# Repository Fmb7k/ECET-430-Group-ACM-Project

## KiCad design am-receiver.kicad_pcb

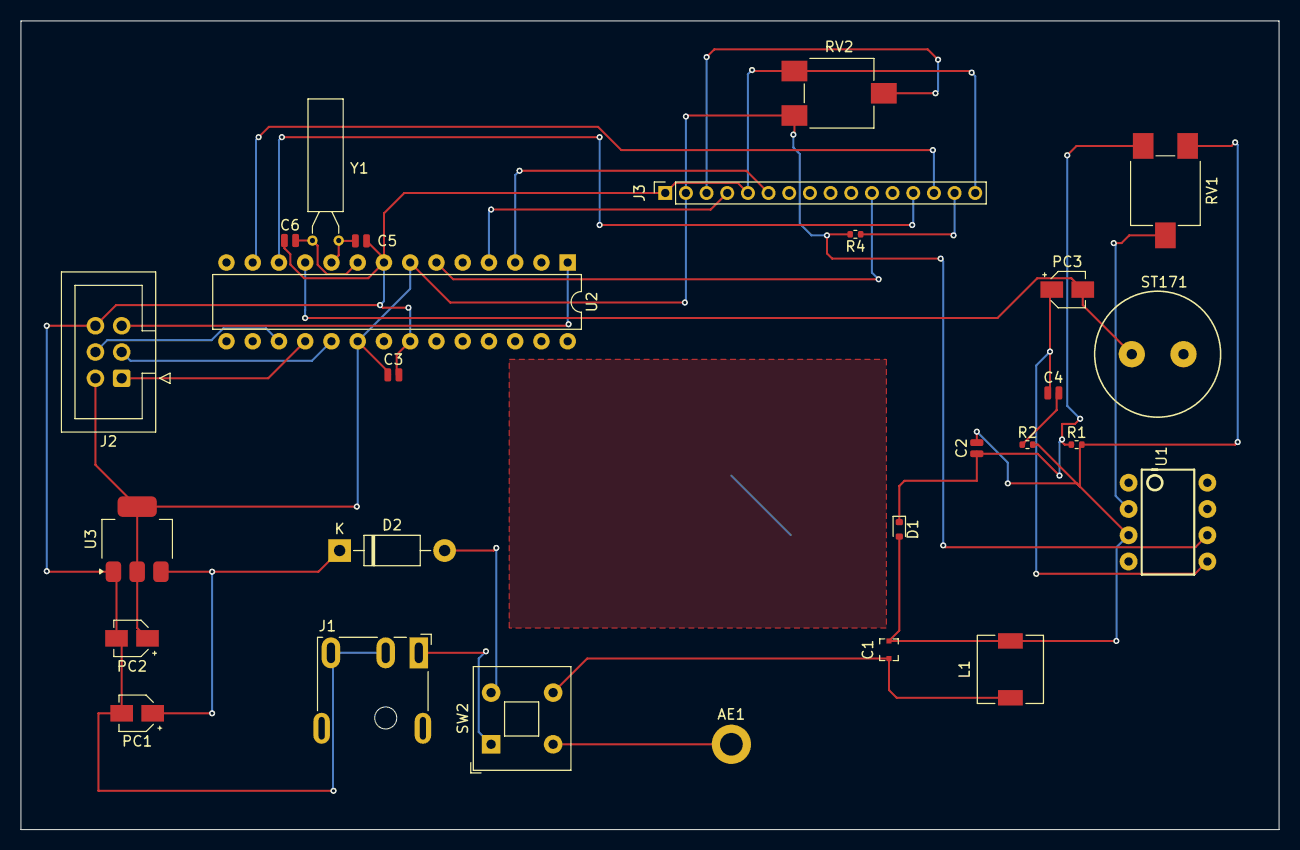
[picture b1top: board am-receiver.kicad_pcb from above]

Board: 2 copper layers, 121.8 x 78.2 mm, 27 parts (0 on the bottom side), 25 nets.

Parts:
AE1: Antenna; MountingHole_2.2mm_M2_DIN965_Pad
C1: 12-120 pF; C_Trimmer_Murata_TZR1
C2: 4.7n; C_0504_1310Metric
C3: 100n; C_0504_1310Metric
C4: .05u; C_0504_1310Metric
C5, C6: 220p; C_0504_1310Metric
D1: 1N4148WT; D_SOD-523
D2: 1N4007; D_DO-41_SOD81_P10.16mm_Horizontal
J1: Barrel_Jack_Switch; BarrelJack_CUI_PJ-079BH_Horizontal
J2: AVR-ISP-6; IDC-Header_2x03_P2.54mm_Vertical
J3: HD44780 16x2 LCD; PinSocket_1x16_P2.00mm_Vertical
L1: 700u; L_6.3x6.3_H3
PC1, PC2: 47u; CP_Elec_3x5.3
PC3: 250u; CP_Elec_3x5.3
R1: 100k; R_0402_1005Metric
R2: 10; R_0402_1005Metric
R4: 220; R_0402_1005Metric
RV1, RV2: 10K Pot; Potentiometer_ACP_CA6-VSMD_Vertical
ST171: Speaker; PS12
SW2: SW_DPST; SW_Push_2P1T_Toggle_CK_PVA1xxH1xxxxxxV2
U1: LM386; DIP08
U2: ATmega328-P; DIP-28_W7.62mm
U3: NCP1117-5.0_SOT223; SOT-223-3_TabPin2
Y1: 16MHz; Crystal_AT310_D3.0mm_L10.0mm_Horizontal

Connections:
FreqRead Input: PC3.2, ST171.P$1, U2.11 (PD5)
GND: C1.2, C2.2, C3.2, C5.1, C6.1, D1.2 (A), J1.2, J1.3, J2.6 (GND), J3.1 (VSS), J3.5 (RW), J3.16 (K), L1.2, PC1.2, PC2.2, R1.2, R2.2, RV1.3, RV2.3, ST171.P$2, U1.3 (+), U1.4 (GND), U2.8 (GND), U2.22 (GND), U3.1 (GND)
MISO: J2.1 (MISO), U2.18 (PB4)
MOSI: J2.4 (MOSI), U2.17 (PB3)
unnamed: AE1.1 (A), SW2.3
unnamed: C1.1, L1.1, SW2.4
unnamed: C4.1, PC3.1, U1.5
unnamed: C4.2, R2.1
unnamed: C2.1, D1.1 (K), R1.1, RV1.1
unnamed: D2.2 (A), SW2.2
unnamed: D2.1 (K), PC1.1, U3.3 (VI)
unnamed: J1.1, SW2.1
unnamed: J3.15 (A), R4.1
unnamed: J3.11 (DB4), U2.6 (PD4)
unnamed: J3.13 (DB6), U2.12 (PD6)
unnamed: J3.14 (DB7), U2.13 (PD7)
unnamed: J3.6 (E), U2.3 (PD1)
unnamed: J3.4 (RS), U2.4 (PD2)
unnamed: J3.3 (VO), RV2.2
unnamed: RV1.2, U1.2 (-)
unnamed: C6.2, U2.9 (XTAL1/PB6), Y1.2
unnamed: C5.2, U2.10 (XTAL2/PB7), Y1.1
RST: J2.5 (~RST), U2.1 (~RESET/PC6)
SCK: J2.3 (SCK), U2.19 (PB5)
Vcc: C3.1, J2.2 (VCC), J3.2 (VDD), PC2.1, R4.2, RV2.1, U1.6 (V+), U2.7 (VCC), U2.20 (AVCC), U3.2 (VO)

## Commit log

2025-02-04 Create Logbook
    Pasted Seven's logbook, will be used to keep track of class notes for project, and also project updates
2025-02-04 Create Research Documentation
2025-02-04 Update Logbook
2025-02-10 electrical block diagram for design doc
2025-02-10 Create Design Documents
2025-02-10 Update Design Documents
2025-02-11 Update Research Documentation
2025-04-21 Update Research Documentation
    arduino op-amps link
2025-04-23 KiCad files
    KiCad files
2025-05-14 Add files via upload
    gerber, drill, bom, schematic pdf
2025-05-14 Add files via upload
    updated kicad for final
2025-05-14 3d render png
2025-05-14 frequency counter code
2025-05-14 Create placeholder
